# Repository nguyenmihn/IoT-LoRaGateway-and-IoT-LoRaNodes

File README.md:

# IoT-LoRaGateway-and-IoT-LoRaNodes
Design and implementation of IoT-LoRaGateway and IoT-LoRaNodes applied in a building safety monitoring system (sponsored by ICE Meca Tech, Korea &amp; IoTVision)
# 🔥 Panel Safety Monitoring System (PSMS)

**PSMS** is an embedded IoT project integrating hardware design, firmware, and LoRa/TCP-IP communication to monitor and detect fire risks inside electrical panels.

---

## 📌 Project Overview

- **Goal**: Detect early signs of sparks, smoke, and temperature anomalies in panels.
- **Use cases**: Industrial installations like thermal power plants.
- **Communication**: LoRa for remote, low-power detection; TCP-IP as wired fallback.

---

## ⚙️ Features

- IR Spark + UV Spark sensors  
- IR Temperature sensor + 2-channel K-type thermocouples  
- Smoke sensor with high sensitivity  
- Real-time monitoring and alerting via embedded firmware  
- HMI interface for live data reading  
- LoRa range up to 2 km; Ethernet option  
- Battery backup to ensure operation during power failure

---

## 🧩 Hardware Components

- Custom PCB with sensor interfaces  
- MCU (e.g., STM32 or ESP32) running embedded C/C++ firmware  
- LoRa module (e.g., SX126x series) or Ethernet board  
- Enclosure designed for panel mounting

---

## 🗂 Repository Structure (Example)

├── hardware/ # PCB schematics, Gerbers, BOM

├── firmware/ # MCU code (C/C++), sensor drivers, LoRa/TCP‑IP stack

├── gateway/ # LoRa gateway or server-side interface code

└── README.md # This file

yaml
Sao chép
Chỉnh sửa

---

## 🚀 Quick Start

1. **Hardware setup**:  
   Assemble PCB, connect sensors, LoRa/Ethernet, and battery backup.

2. **Build firmware**:  
   ```bash
   cd firmware
   make all
hoặc dùng PlatformIO / STM32CubeIDE.

Configure LoRa:

Set frequency (433MHz)

Configure gateway addresses

Enable TCP-IP if used

Deploy HMI:
Copy firmware/ui files lên HMI panel.

Test & Calibrate:
Verify readings, range test LoRa, simulate spark/smoke.

✅ Deployed Example
Installed in Yeongheung Thermal Power Plant (Unit #5, 870 MW)

Runs under KOEN-supported R&D project (Dec 2022–Dec 2024)

🛠 Tech Stack
MCU: STM32/ESP32 with firmware in C/C++

Communication: LoRa (Semtech SX126x), TCP/IP Ethernet module

Sensors: IR/UV spark, temperature, thermocouple, smoke

Build tools: Makefile or PlatformIO / STM32CubeIDE

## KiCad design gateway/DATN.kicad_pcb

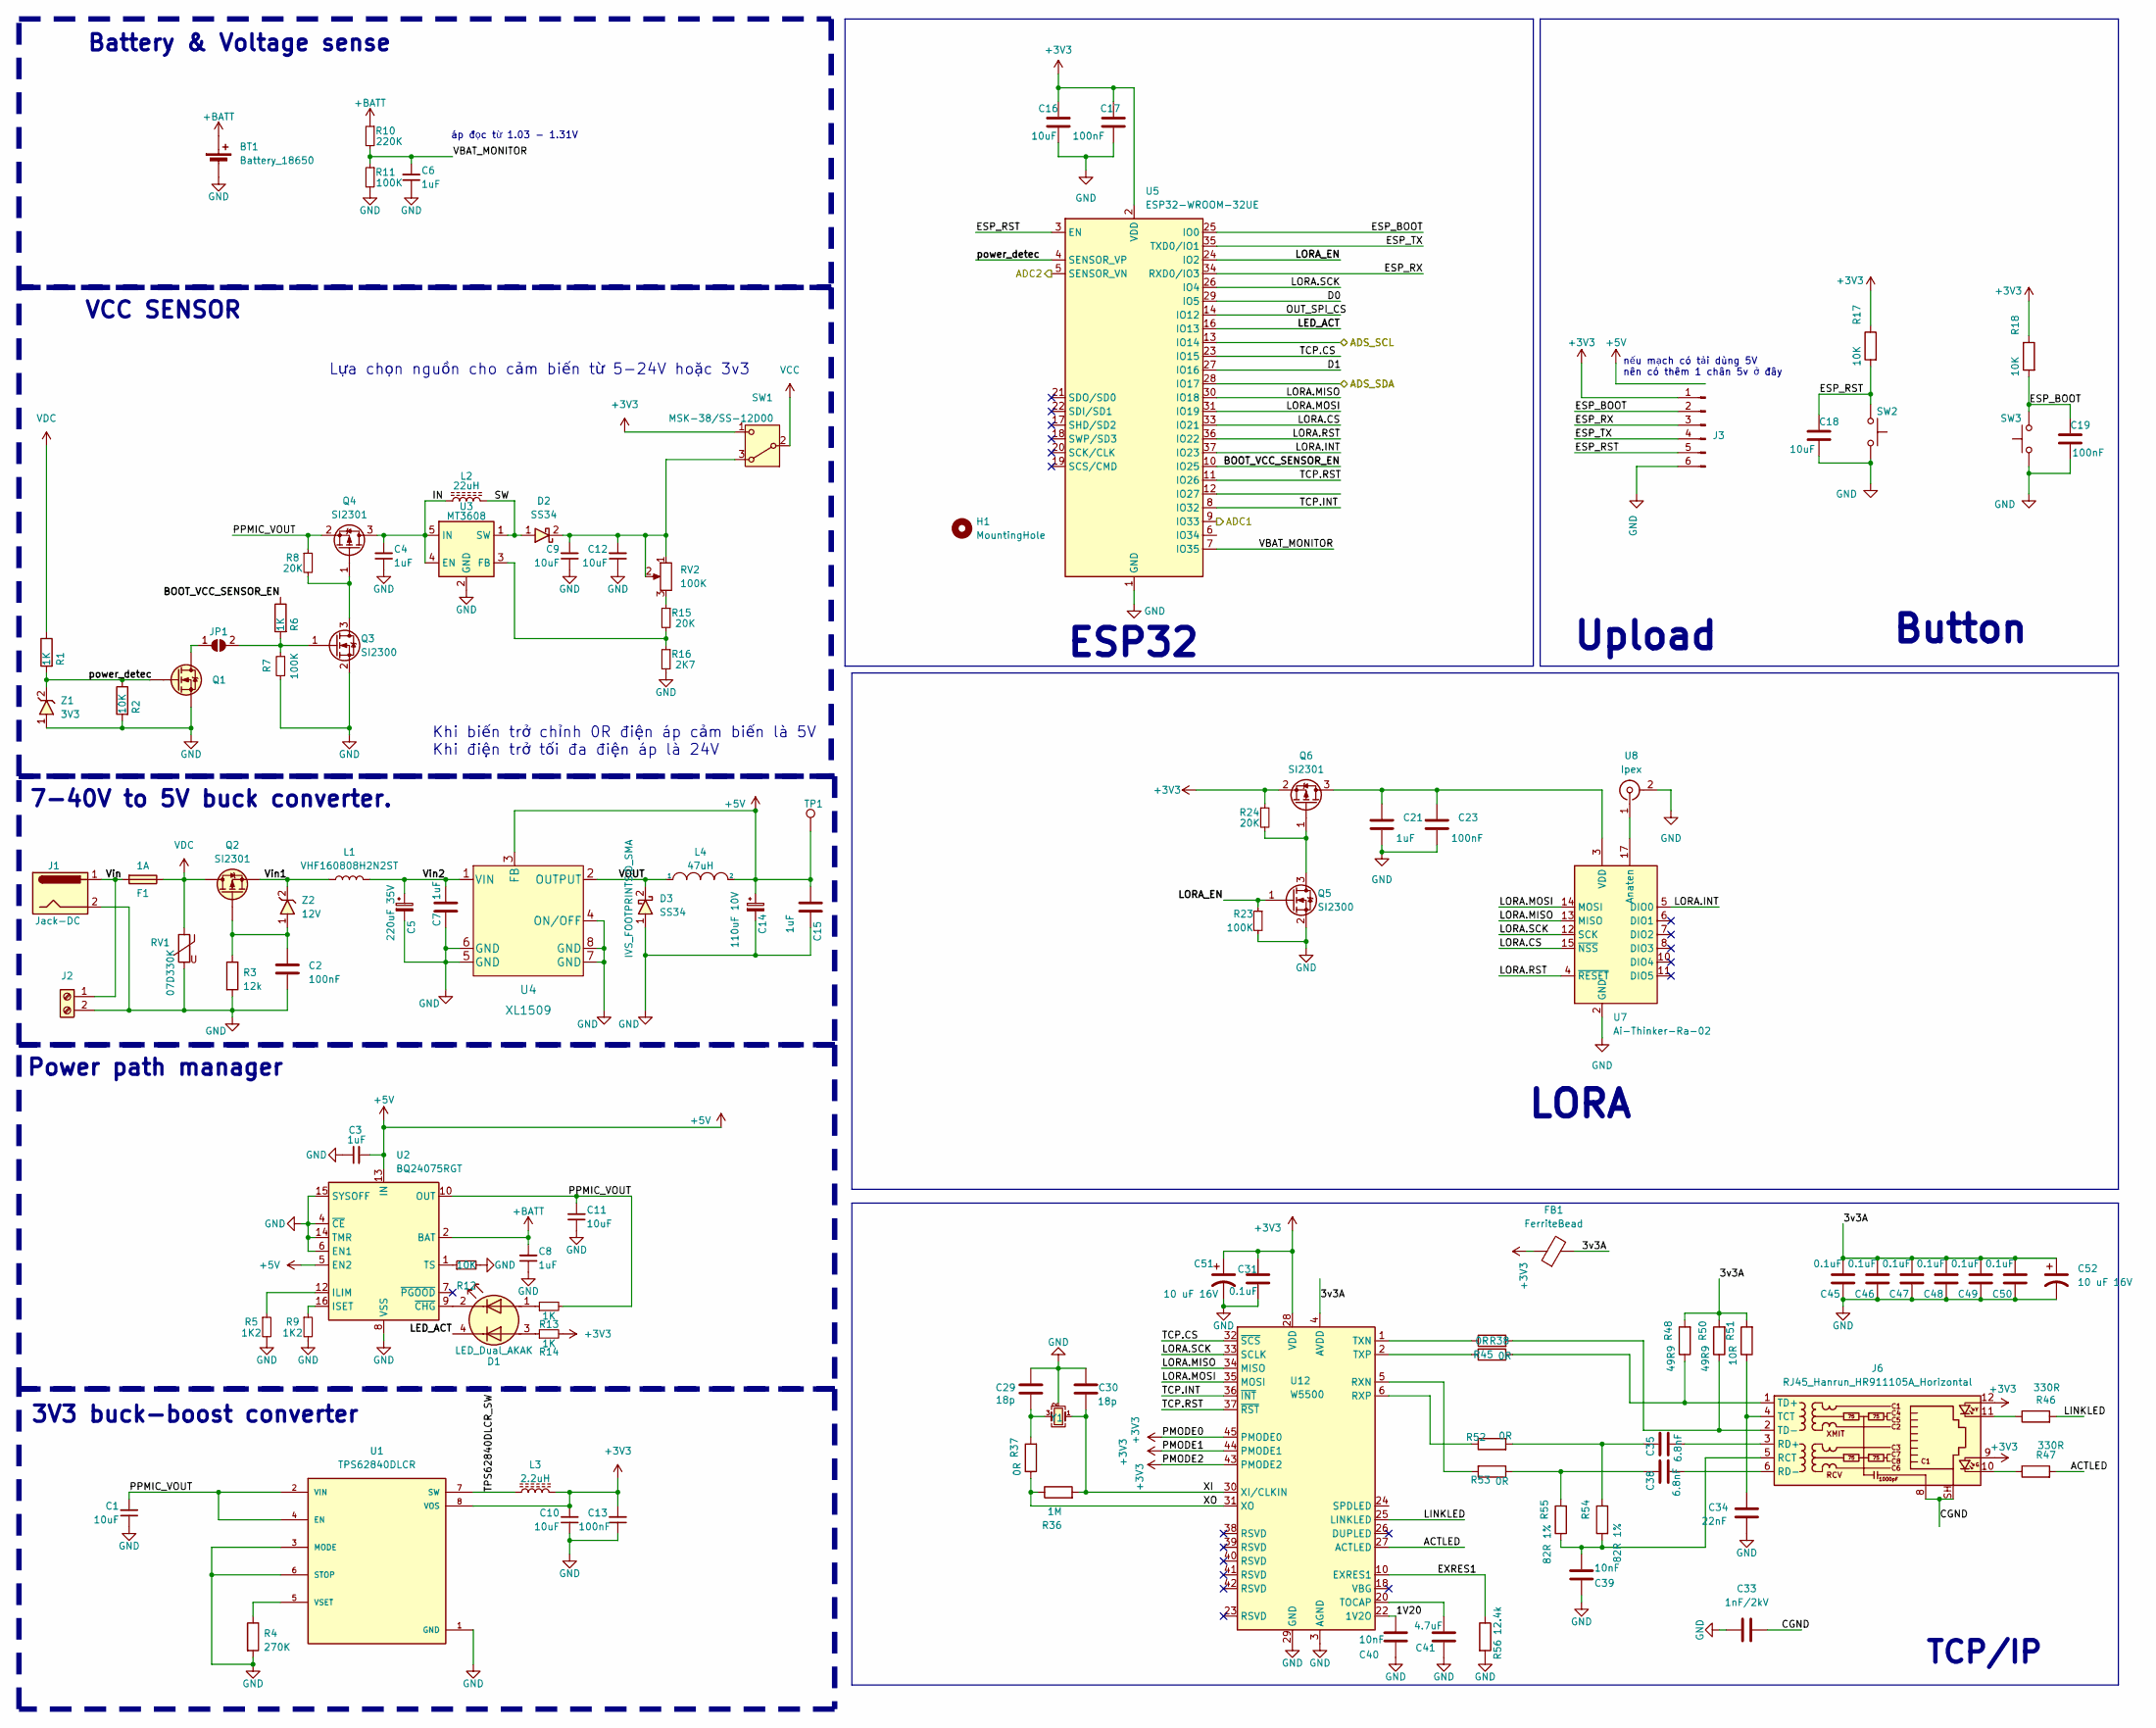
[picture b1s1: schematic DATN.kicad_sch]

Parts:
BT1: Battery_18650; XH 2.54 2Pin Female
C1, C9, C10, C11, C12, C16, C18: 10uF; C_0603
C2, C13, C17, C19, C23: 100nF; C_0603
C3, C4, C6, C7, C8, C15, C21: 1uF; C_0603
C5: 220uF 35V; CP_Elec_8x10.5
C14: 110uF 10V; CP_Elec_6.3x5.4
C29, C30: 18p; C_0603
C31: 0.1uF; C_0603
C33: 1nF/2kV; C_Disc_D10.0mm_W2.5mm_P5.00mm
C34: 22nF; C_0603
C35, C38: 6.8nF; C_0805
C39, C40: 10nF; C_0603
C41: 4.7uF; C_0603
C45, C46, C47, C48, C49, C50: 0.1uF; C_0805
C51, C52: 10 uF 16V; CP_EIA-3216-10_Kemet-I
D1: LED_Dual_AKAK; LED_Housing_Dual
D2, D3: SS34; D_SMA
F1: 1A; F_1812
FB1: FerriteBead; R_0805_2012Metric
H1: MountingHole; MountingHole_3mm_M4_DIN965_Pad
J1: Jack-DC; BarrelJack_Wuerth_6941xx301002
J2: Screw_Terminal_01x02; KF-5.08-2P
J3: Conn_01x06_Male; PinHeader_1x06_P2.54mm_Vertical
J6: RJ45_Hanrun_HR911105A_Horizontal
JP1: SolderJumper_2_Open; SolderJumper-2_P1.3mm_Open_RoundedPad1.0x1.5mm
L1: VHF160808H2N2ST; L_0603_1608Metric
L2: 22uH; L_Bourns_SRN6045TA
L3: 2.2uH; L_Bourns_SRN6045TA
L4: 47uH; L_7.3x7.3_H4.5
Q1, Q3, Q5: SI2300; SOT23-3
Q2, Q4, Q6: SI2301; SOT23-3
R1, R6, R13, R14: 1K; R_0603
R2, R12, R17, R18: 10K; R_0603
R3: 12k; R_0603
R4: 270K; R_0603
R5, R9: 1K2; R_0603
R7, R11, R23: 100K; R_0603
R8, R15, R24: 20K; R_0603
R10: 220K; R_0603
R16: 2K7; R_0603
R36: 1M; R_0603
R37, R38, R45, R52, R53: 0R; R_0603
R46, R47: 330R; R_0603
R48, R50: 49R9; R_0603
R51: 10R; R_0805
R54, R55: 82R 1%; R_0805
R56: 12.4k; R_0603
RV1: 07D330K; RV_Disc_D12mm_W4.2mm_P7.5mm
RV2: 100K; Potentiometer_Bourns_TC33X_Vertical
SW1: MSK-38/SS-12D00; SW_MSK-38
SW2: SW_Push; SW_SPST_B3U-1000P
SW3: SW_Push; SW_6x6_90DEG
TP1: TestPoint; TestPoint_Pad_D1.0mm
U1: TPS62840DLCR; VSON-HR - 1 mm
U2: BQ24075RGT; VQFN-16-1EP_3x3mm_P0.5mm_EP1.6x1.6mm_ThermalVias
U3: MT3608; SOT-23-6
U4: XL1509; SOIC-8_3.9x4.9mm_P1.27mm
U5: ESP32-WROOM-32UE; ESP32-WROOM-32E
U7: Ai-Thinker-Ra-02; MODULE_RA-02_LORA
U8: Ipex; Connector_Coaxial_SMA
U12: W5500; LQFP-48_7x7mm_P0.5mm
Y1: Crystal_MCU; Crystal_3225_4P_3.2x2.6mm
Z1: 3V3; D_SOD-123
Z2: 12V; D_SOD-123

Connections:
+3V3: C10.2, C13.2, C16.1, C17.1, C31.1, C51.1, FB1.1, J3.1, J6.9, J6.12, L3.2, Q6.2 (S), R14.2, R17.1, R18.1, R24.1, SW1.1 (C), U1.8 (VOS), U5.2 (VDD), U12.28 (VDD), U12.43 (PMODE2), U12.44 (PMODE1), U12.45 (PMODE0)
+5V: C3.2, C14.1, C15.2, L4.2, TP1.1, U2.5 (EN2), U2.13 (IN), U4.3 (FB)
+BATT: BT1.1 (+), C8.2, R10.1, U2.2 (BAT), U2.3 (BAT)
/1V20: C40.2, U12.22 (1V2O)
/3v3A: C45.2, C46.2, C47.2, C48.2, C49.2, C50.2, C52.1, FB1.2, R48.2, R50.2, R51.2, U12.4 (AVDD), U12.8 (AVDD), U12.11 (AVDD), U12.15 (AVDD), U12.17 (AVDD), U12.21 (AVDD)
/ACTLED: R47.2, U12.27 (ACTLED)
/ADC1: U5.9 (IO33)
/ADC2: U5.5 (SENSOR_VN)
/ADS_SCL: U5.13 (IO14)
/ADS_SDA: U5.28 (IO17)
/BOOT_VCC_SENSOR_EN: R6.1, U5.10 (IO25)
/CGND: C33.2, J6.8, J6.SH
/D0: U5.29 (IO5)
/D1: U5.27 (IO16)
/ESP_BOOT: C19.1, J3.2, R18.2, SW3.2, U5.25 (IO0)
/ESP_RST: C18.1, J3.5, R17.2, SW2.2, U5.3 (EN)
/ESP_RX: J3.3, U5.34 (RXD0/IO3)
/ESP_TX: J3.4, U5.35 (TXD0/IO1)
/EXRES1: R56.1, U12.10 (EXRES1)
/IN: C4.2, L2.1, Q4.3 (D), U3.4 (EN), U3.5 (IN)
/LED_ACT: D1.4 (K2), U5.16 (IO13)
/LINKLED: R46.2, U12.25 (LINKLED)
/LORA.CS: U5.33 (IO21), U7.15 (~NSS)
/LORA.INT: U5.37 (IO23), U7.5 (DIO0)
/LORA.MISO: U5.30 (IO18), U7.13 (MISO), U12.34 (MISO)
/LORA.MOSI: U5.31 (IO19), U7.14 (MOSI), U12.35 (MOSI)
/LORA.RST: U5.36 (IO22), U7.4 (~RESET)
/LORA.SCK: U5.26 (IO4), U7.12 (SCK), U12.33 (SCLK)
/LORA_EN: Q5.1 (G), R23.1, U5.24 (IO2)
/OUT_SPI_CS: U5.14 (IO12)
/PPMIC_VOUT: C1.2, C11.2, Q4.2 (S), R8.1, R13.2, U1.2 (VIN), U1.4 (EN), U2.10 (OUT), U2.11 (OUT)
/SW: D2.1, L2.2, U3.1 (SW)
/TCP.CS: U5.23 (IO15), U12.32 (~SCS)
/TCP.INT: U5.8 (IO32), U12.36 (~INT)
/TCP.RST: U5.11 (IO26), U12.37 (~RST)
/TPS62840DLCR_SW: L3.1, U1.7 (SW)
/VBAT_MONITOR: C6.2, R10.2, R11.1, U5.7 (IO35)
/VOUT: D3.2, L4.1, U4.2 (OUTPUT)
/Vin: F1.1, J1.1, J2.1
/Vin1: L1.1, Q2.2 (S), Z2.2
/Vin2: C5.1, C7.2, L1.2, U4.1 (VIN)
/XI: C30.2, R36.2, U12.30 (XI/CLKIN), Y1.1
/XO: R36.1, R37.1, U12.31 (XO)
/power_detec: Q1.1 (G), R1.2, R2.1, U5.4 (SENSOR_VP), Z1.2
GND: BT1.2 (-), C1.1, C2.2, C3.1, C4.1, C5.2, C6.1, C7.1, C8.1, C9.1, C10.1, C11.1, C12.1, C13.1, C14.2, C15.1, C16.2, C17.2, C18.2, C19.2, C21.2, C23.2, C29.1, C30.1, C31.2, C33.1, C34.2, C39.1, C40.1, C41.1, C45.1, C46.1, C47.1, C48.1, C49.1, C50.1, C51.2, C52.2, D3.1, J1.2, J2.2, J3.6, Q1.2 (S), Q3.2 (S), Q5.2 (S), R2.2, R3.2, R4.2, R5.2, R7.2, R9.2, R11.2, R12.2, R16.2, R23.2, R56.2, RV1.2, SW2.1, SW3.1, U1.1 (GND), U1.3 (MODE), U1.6 (STOP), U2.4 (~CE), U2.6 (EN1), U2.8 (VSS), U2.14 (TMR), U2.15 (SYSOFF), U2.17 (VSS), U3.2 (GND), U4.4 (ON/OFF), U4.5 (GND), U4.6 (GND), U4.7 (GND), U4.8 (GND), U5.1 (GND), U5.15 (GND), U5.38 (GND), U5.39 (GND), U7.1 (GND), U7.2 (GND), U7.9 (GND), U7.16 (GND), U8.2, U12.3 (AGND), U12.9 (AGND), U12.14 (AGND), U12.16 (AGND), U12.19 (AGND), U12.29 (GND), U12.48 (AGND), Y1.2, Y1.4, Z1.1
unnamed: C29.2, R37.2, Y1.3
unnamed: C35.1, R52.2, R54.2
unnamed: C38.1, R53.1, R55.2
unnamed: D1.1 (A1), R13.1
unnamed: D1.3 (A2), R14.1
unnamed: D1.2 (K1), U2.9 (~CHG)
unnamed: J6.10, R47.1
unnamed: J6.11, R46.1
unnamed: C39.2, J6.5 (RCT), R54.1, R55.1
unnamed: C35.2, J6.3 (RD+)
unnamed: C38.2, J6.6 (RD-)
unnamed: C34.1, J6.4 (TCT), R51.1
unnamed: J6.1 (TD+), R45.1, R48.1
unnamed: J6.2 (TD-), R38.2, R50.1
unnamed: JP1.1 (A), Q1.3 (D)
unnamed: JP1.2 (B), Q3.1 (G), R6.2, R7.1
unnamed: C2.1, Q2.1 (G), R3.1, Z2.1
unnamed: Q3.3 (D), Q4.1 (G), R8.2
unnamed: Q5.3 (D), Q6.1 (G), R24.2
unnamed: C21.1, C23.1, Q6.3 (D), U7.3 (VDD)
unnamed: R15.1, RV2.3
unnamed: C9.2, C12.2, D2.2, RV2.1, RV2.2, SW1.3 (A)
unnamed: R4.1, U1.5 (VSET)
unnamed: R5.1, U2.12 (ILIM)
unnamed: R9.1, U2.16 (ISET)
unnamed: R12.1, U2.1 (TS)
unnamed: R15.2, R16.1, U3.3 (FB)
unnamed: U7.17 (Anaten), U8.1
unnamed: R53.2, U12.5 (RXN)
unnamed: R52.1, U12.6 (RXP)
unnamed: C41.2, U12.20 (TOCAP)
unnamed: R38.1, U12.1 (TXN)
unnamed: R45.2, U12.2 (TXP)
VCC: SW1.2 (B)
VDC: F1.2, Q2.3 (D), R1.1, RV1.1

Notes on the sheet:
VCC SENSOR
LORA
Lựa chọn nguồn cho cảm biến từ 5-24V hoặc 3v3
3V3 buck-boost converter
Khi biến trở chỉnh 0R điện áp cảm biến là 5V Khi điện trở tối đa điện áp là 24V
nếu mạch có tải dùng 5V nên có thêm 1 chân 5v ở đây
áp đọc từ 1.03 - 1.31V
Button
Upload
Power path manager
ESP32
TCP/IP
7-40V to 5V buck converter.
Battery & Voltage sense

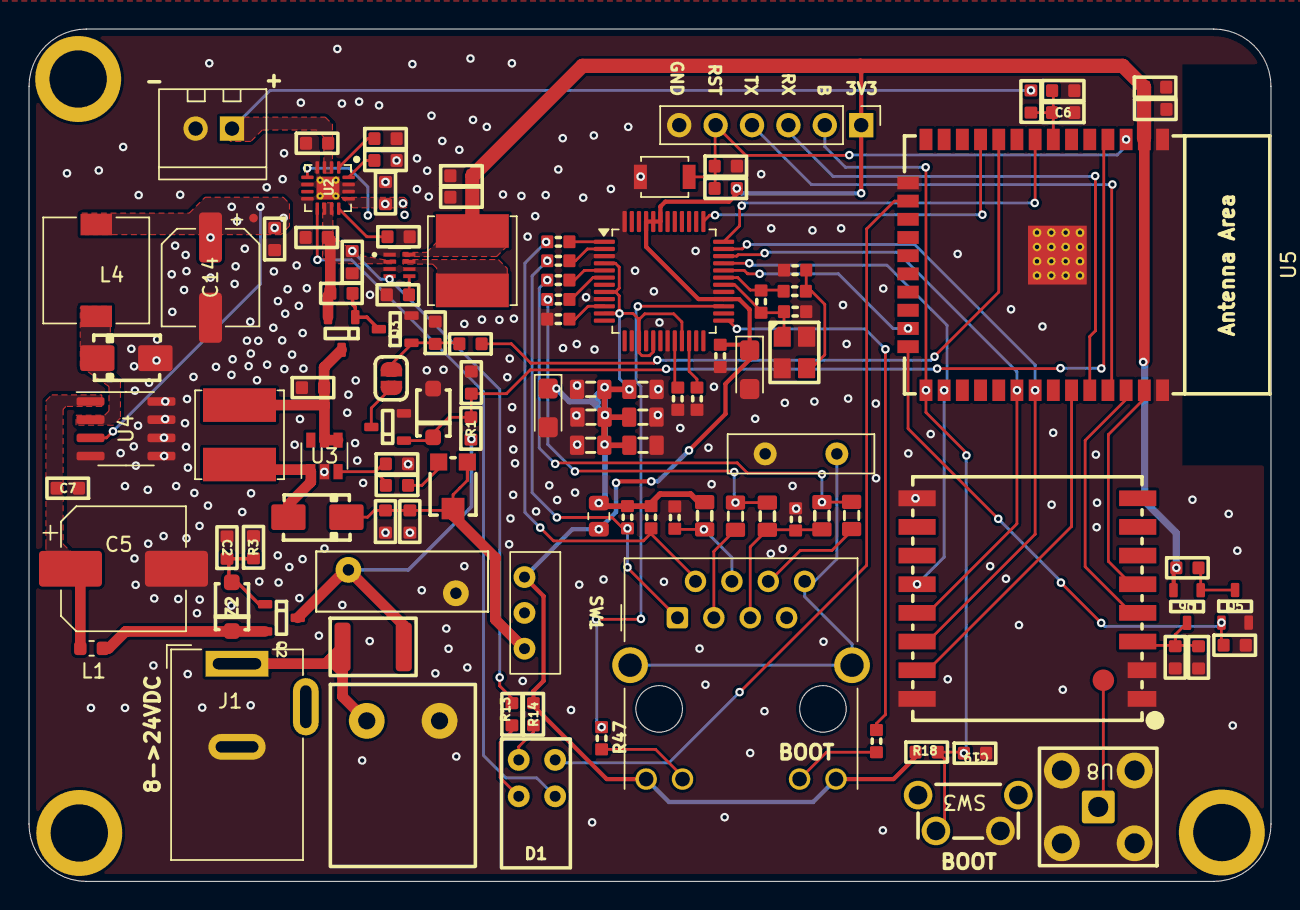
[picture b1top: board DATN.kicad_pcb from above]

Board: 2 copper layers, 86.7 x 59.5 mm, 112 parts (1 on the bottom side), 72 nets.

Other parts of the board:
Designed by Nguyễn Đình Nhật Minh: LOGO; IoTVision_NewLoGo_30.9x8

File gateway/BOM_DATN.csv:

#,Reference,Value,Datasheet,Footprint,Qty,DNP
1,BT1,Battery_18650,~,IVS_FOOTPRINTS:XH 2.54 2Pin Female,1,
2,"C1,C9,C10,C11,C12,C16,C18",10uF,~,IVS_FOOTPRINTS:C_0603,7,https://www.thegioiic.com/tu-gom-0603-10uf-25v
3,"C2,C13,C17,C19,C23",100nF,~,IVS_FOOTPRINTS:C_0603,5,https://www.thegioiic.com/tu-gom-0603-100nf-0-1uf-50v
4,"C3,C4,C6,C7,C8,C15,C21",1uF,~,IVS_FOOTPRINTS:C_0603,7,https://www.thegioiic.com/tu-gom-0603-1uf-50v
5,C5,220uF 35V,~,Capacitor_SMD:CP_Elec_8x10.5,1,https://www.thegioiic.com/tu-nhom-smd-220uf-35v-8x10-5mm
6,C14,110uF 10V,~,Capacitor_SMD:CP_Elec_6.3x5.4,1,https://www.thegioiic.com/tu-nhom-smd-330uf-6-3v-6-3x7-7mm
7,"C29,C30",18p,~,IVS_FOOTPRINTS:C_0603,2,https://www.thegioiic.com/tu-gom-0603-18pf-50v
8,"C31,C45,C46,C47,C48,C49,C50",0.1uF,~,-- mixed values --,7,
9,C33,1nF/2kV,~,Capacitor_THT:C_Disc_D10.0mm_W2.5mm_P5.00mm,1,
10,C34,22nF,~,IVS_FOOTPRINTS:C_0603,1,https://www.thegioiic.com/tu-gom-0603-22nf-50v
11,"C35,C38",6.8nF,~,IVS_FOOTPRINTS:C_0805,2,https://www.thegioiic.com/tu-gom-0805-6-8nf-50v
12,"C39,C40",10nF,~,IVS_FOOTPRINTS:C_0603,2,https://www.thegioiic.com/tu-gom-0603-10nf-50v
13,C41,4.7uF,~,IVS_FOOTPRINTS:C_0603,1,
14,"C51,C52",10 uF 16V,~,Capacitor_Tantalum_SMD:CP_EIA-3216-10_Kemet-I,2,
15,D1,LED_Dual_AKAK,~,IVS_FOOTPRINTS:LED_Housing_Dual,1,https://www.thegioiic.com/bo-chi-thi-2-led-xanh-la-do-3mm-de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
16,"D2,D3",SS34,,IVS_FOOTPRINTS:D_SMA,2,https://www.thegioiic.com/twgmc-ss34-sma-diode-schottky-3a
17,F1,1A,~,IVS_FOOTPRINTS:F_1812,1,https://www.thegioiic.com/mf-msmf020-2-cau-chi-tu-phuc-hoi-1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
18,FB1,FerriteBead,~,IVS_FOOTPRINTS:R_0805_2012Metric,1,
19,H1,MountingHole,~,minh_iot:MountingHole_3mm_M4_DIN965_Pad,1,
20,J1,Jack-DC,~,Connector_BarrelJack:BarrelJack_Wuerth_6941xx301002,1,https://www.thegioiic.com/dc5521-dau-noi-nguon-dc-cai-5521-h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
21,J2,Screw_Terminal_01x02,~,IVS_FOOTPRINTS:KF-5.08-2P,1,
22,J3,Conn_01x06_Male,~,Connector_PinHeader_2.54mm:PinHeader_1x06_P2.54mm_Vertical,1,
23,J6,RJ45_Hanrun_HR911105A_Horizontal,https://datasheet.lcsc.com/lcsc/1811141815_HANRUN-Zhongshan-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,Connector_RJ:RJ45_Hanrun_HR911105A_Horizontal,1,
24,JP1,SolderJumper_2_Open,~,IVS_FOOTPRINTS:SolderJumper-2_P1.3mm_Open_RoundedPad1.0x1.5mm,1,
25,L1,VHF160808H2N2ST,~,Inductor_SMD:L_0603_1608Metric,1,https://www.thegioiic.com/vhf160808h2n2st-cuon-cam-2-2nh-0603-1a
26,L2,22uH,~,Inductor_SMD:L_Bourns_SRN6045TA,1,https://www.thegioiic.com/cuon-cam-dan-smd-cd53-5852-220-22uh-1-5a
27,L3,2.2uH,~,Inductor_SMD:L_Bourns_SRN6045TA,1,
28,L4,47uH,~,IVS_FOOTPRINTS:L_7.3x7.3_H4.5,1,https://www.thegioiic.com/cuon-cam-dan-smd-cdrh74-7345-470-4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
29,"Q1,Q3,Q5",SI2300,-- mixed values --,IVS_FOOTPRINTS:SOT23-3,3,https://www.thegioiic.com/si2300ds-mosfet-kenh-n-30v-3-6a-sot-23
30,"Q2,Q4,Q6",SI2301,-- mixed values --,IVS_FOOTPRINTS:SOT23-3,3,https://www.thegioiic.com/si2301ds-mosfet-kenh-p-20v-2-3a-sot-23-3
31,"R1,R6,R13,R14",1K,~,IVS_FOOTPRINTS:R_0603,4,
32,"R2,R12,R17,R18",10K,~,IVS_FOOTPRINTS:R_0603,4,
33,R3,12k,~,IVS_FOOTPRINTS:R_0603,1,
34,R4,270K,~,IVS_FOOTPRINTS:R_0603,1,
35,"R5,R9",1K2,~,IVS_FOOTPRINTS:R_0603,2,
36,"R7,R11,R23,RV2",100K,~,-- mixed values --,4,
37,"R8,R15,R24",20K,~,IVS_FOOTPRINTS:R_0603,3,
38,R10,220K,~,IVS_FOOTPRINTS:R_0603,1,
39,R16,2K7,~,IVS_FOOTPRINTS:R_0603,1,
40,R36,1M,~,IVS_FOOTPRINTS:R_0603,1,
41,"R37,R38,R45,R52,R53",0R,~,IVS_FOOTPRINTS:R_0603,5,
42,"R46,R47",330R,~,IVS_FOOTPRINTS:R_0603,2,
43,"R48,R50",49R9,~,IVS_FOOTPRINTS:R_0603,2,
44,R51,10R,~,IVS_FOOTPRINTS:R_0805,1,
45,"R54,R55",82R 1%,~,IVS_FOOTPRINTS:R_0805,2,
46,R56,12.4k,~,IVS_FOOTPRINTS:R_0603,1,
47,RV1,07D330K,~,Varistor:RV_Disc_D12mm_W4.2mm_P7.5mm,1,https://www.thegioiic.com/tu-chong-set-varistor-07d330k-33v
48,SW1,MSK-38/SS-12D00,https://www.nidec-components.com/e/catalog/switch/cas.pdf,IVS_FOOTPRINTS:SW_MSK-38,1,
49,"SW2,SW3",SW_Push,~,-- mixed values --,2,
50,TP1,TestPoint,~,IVS_FOOTPRINTS:TestPoint_Pad_D1.0mm,1,
51,U1,TPS62840DLCR,,IVS_FOOTPRINTS:VSON-HR - 1 mm,1,
52,U2,BQ24075RGT,http://www.ti.com/lit/ds/symlink/bq24075.pdf,IVS_FOOTPRINTS:VQFN-16-1EP_3x3mm_P0.5mm_EP1.6x1.6mm_ThermalVias,1,
53,U3,MT3608,https://www.olimex.com/Products/Breadboarding/BB-PWR-3608/re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,IVS_FOOTPRINTS:SOT-23-6,1,https://www.thegioiic.com/mt3608-ic-dieu-chinh-tang-ap-2a-sot-23-6
54,U4,XL1509,https://datasheet.lcsc.com/lcsc/1809050422_XLSEMI-XL1509-5-0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,IVS_FOOTPRINTS:SOIC-8_3.9x4.9mm_P1.27mm,1,https://www.thegioiic.com/xl1509-5-0e1-ic-on-ap-5v-2a-8-soic
55,U5,ESP32-WROOM-32UE,https://www.espressif.com/sites/default/files/documentation/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,IVS_FOOTPRINTS:ESP32-WROOM-32E,1,https://www.thegioiic.com/esp32-wroom-32e-n4-module-wifi-blu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
56,U7,Ai-Thinker-Ra-02,http://wiki.ai-thinker.com/_media/lora/docs/c048ps01a1_ra-02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,IVS_FOOTPRINTS:MODULE_RA-02_LORA,1,https://www.thegioiic.com/sx1278-lora-ra-02-ai-thinker-mach-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
57,U8,Ipex,https://datasheet.lcsc.com/lcsc/1811091710_HRS-Hirose-U-FL-R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,IVS_FOOTPRINTS:Connector_Coaxial_SMA,1,https://www.thegioiic.com/ahcg-204-cong-rf-ipex-g1-2-chan-dan-smd
58,U12,W5500,http://wizwiki.net/wiki/lib/exe/fetch.php/products:w5500:w55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,Package_QFP:LQFP-48_7x7mm_P0.5mm,1,
59,Y1,Crystal_MCU,https://docs.rs-online.com/ec34/0900766b816028ea.pdf,IVS_FOOTPRINTS:Crystal_3225_4P_3.2x2.6mm,1,
60,Z1,3V3,,IVS_FOOTPRINTS:D_SOD-123,1,https://www.thegioiic.com/bzt52c5v1-diode-zener-5-1v-500mw
61,Z2,12V,,IVS_FOOTPRINTS:D_SOD-123,1,

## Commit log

2025-07-14 Create LICENSE
